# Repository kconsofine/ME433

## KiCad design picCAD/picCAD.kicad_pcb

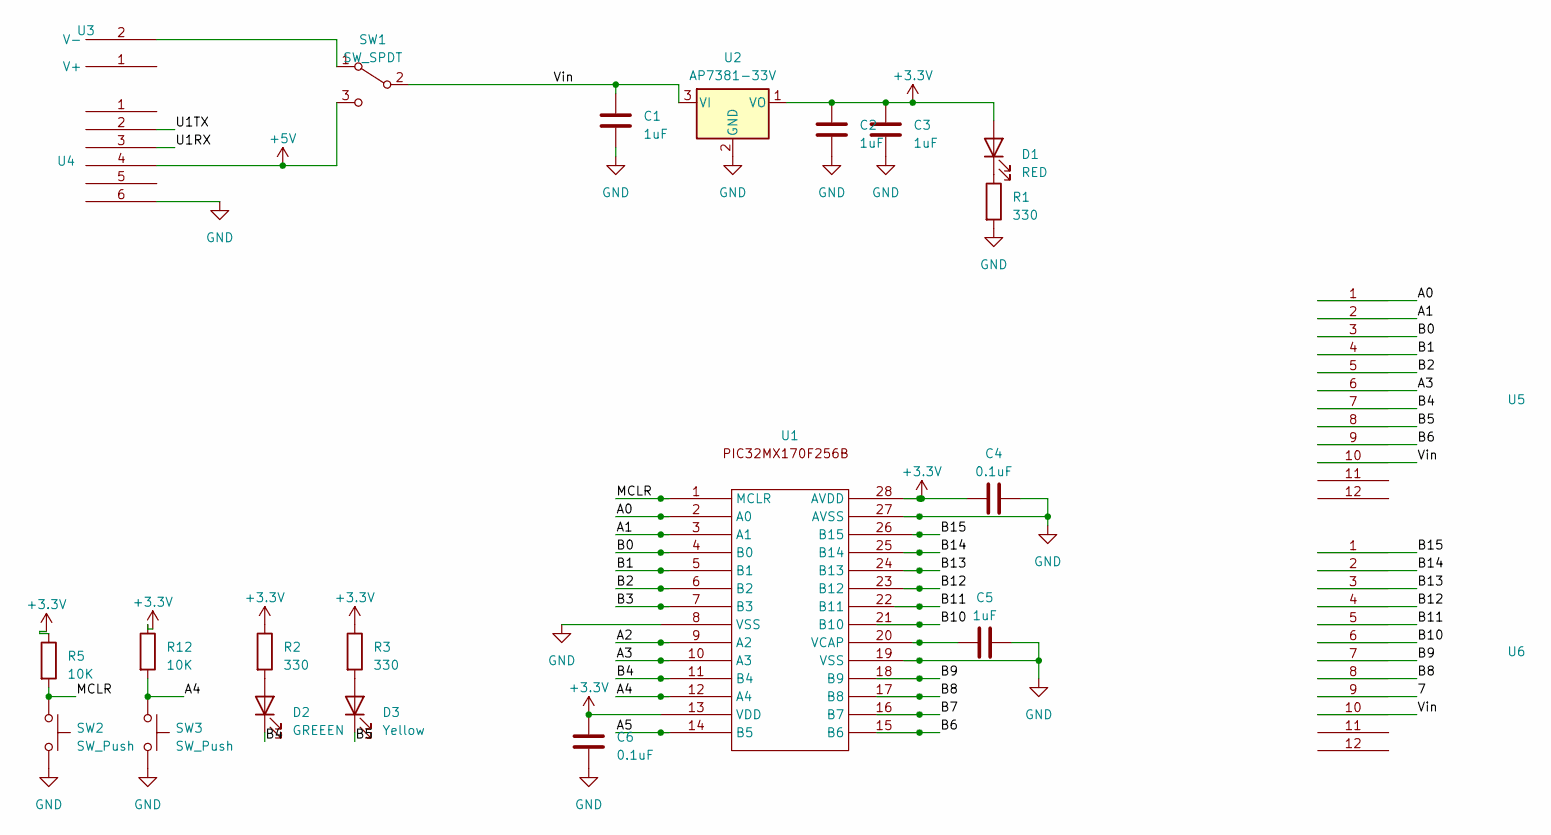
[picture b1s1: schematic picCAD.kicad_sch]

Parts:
C1, C2, C3, C5: 1uF; C_Disc_D3.8mm_W2.6mm_P2.50mm
C4, C6: 0.1uF; C_Disc_D3.8mm_W2.6mm_P2.50mm
D1: RED; LED_D3.0mm
D2: GREEEN; LED_D3.0mm
D3: Yellow; LED_D3.0mm
R1, R2, R3: 330; R_Axial_DIN0207_L6.3mm_D2.5mm_P7.62mm_Horizontal
R5, R12: 10K; R_Axial_DIN0207_L6.3mm_D2.5mm_P7.62mm_Horizontal
SW1: SW_SPDT; slide2
SW2, SW3: SW_Push; push button
U1: DIP-28_W7.62mm_Socket
U2: AP7381-33V; TO-92L_Inline
U3: PinSocket_1x02_P2.54mm_Vertical
U4: PinSocket_1x06_P2.54mm_Vertical
U5, U6: PinSocket_1x12_P2.54mm_Vertical

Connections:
+3.3V: C2.1, C3.1, C4.1, C6.2, D1.2 (A), R2.1, R3.1, R5.1, R12.1, U1.13 (VDD), U1.28 (AVDD), U2.1 (VO)
+5V: SW1.3 (C), U4.4
/7: U6.9
/A0: U1.2 (A0), U5.1
/A1: U1.3 (A1), U5.2
/A2: U1.9 (A2)
/A3: U1.10 (A3), U5.6
/A4: R12.2, SW3.1, U1.12 (A4)
/A5: U1.14 (B5)
/B0: U1.4 (B0), U5.3
/B1: U1.5 (B1), U5.4
/B2: U1.6 (B2), U5.5
/B3: U1.7 (B3)
/B4: D2.1 (K), U1.11 (B4), U5.7
/B5: D3.1 (K), U5.8
/B6: U1.15 (B6), U5.9
/B7: U1.16 (B7)
/B8: U1.17 (B8), U6.8
/B9: U1.18 (B9), U6.7
/B10: U1.21 (B10), U6.6
/B11: U1.22 (B11), U6.5
/B12: U1.23 (B12), U6.4
/B13: U1.24 (B13), U6.3
/B14: U1.25 (B14), U6.2
/B15: U1.26 (B15), U6.1
/MCLR: R5.2, SW2.1, U1.1 (MCLR)
/U1RX: U4.3
/U1TX: U4.2
/Vin: C1.1, SW1.2 (B), U2.3 (VI), U5.10, U6.10
GND: C1.2, C2.2, C3.2, C4.2, C5.2, C6.1, R1.2, SW2.2, SW3.2, U1.8 (VSS), U1.19 (VSS), U1.27 (AVSS), U2.2 (GND), U4.6
unnamed: D1.1 (K), R1.1
unnamed: D2.2 (A), R2.2
unnamed: D3.2 (A), R3.2
unnamed: SW1.1 (A), U3.2 (V-)
unnamed: C5.1, U1.20 (VCAP)

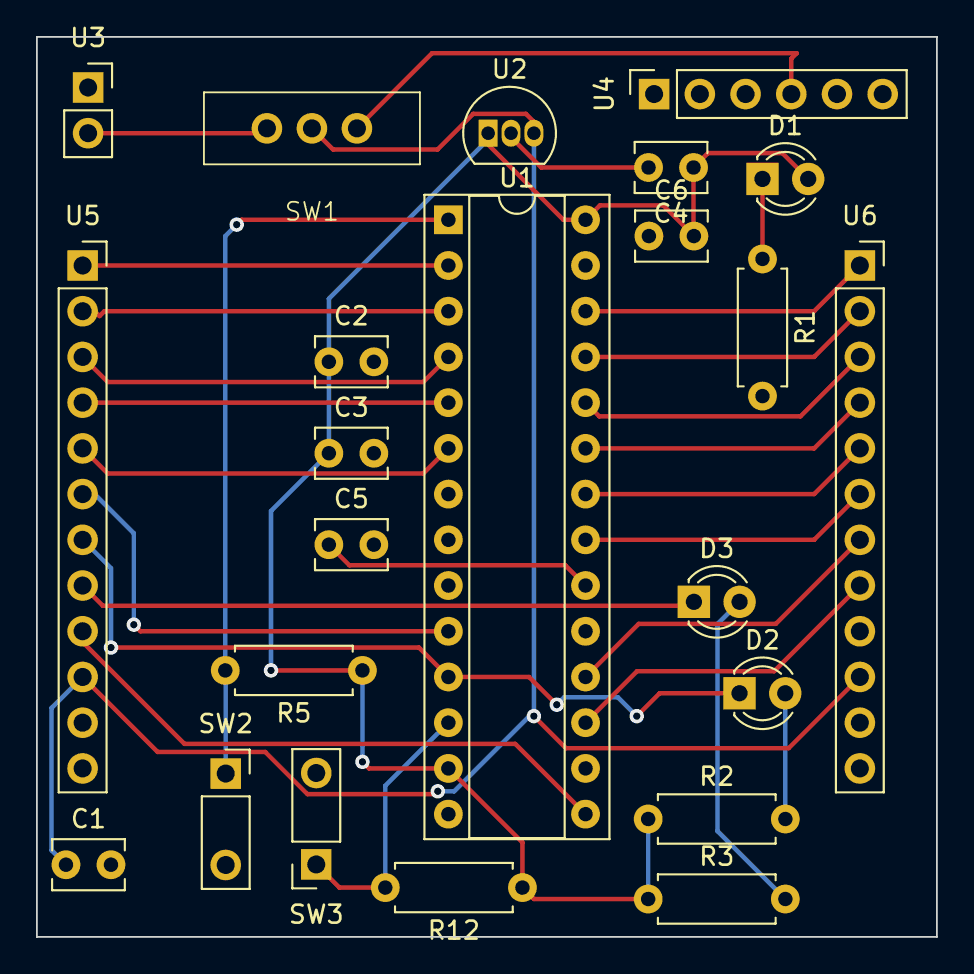
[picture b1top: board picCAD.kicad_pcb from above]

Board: 2 copper layers, 50.0 x 50.0 mm, 23 parts (0 on the bottom side), 28 nets.

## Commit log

2023-04-19 lkjdsf
2023-04-19 vid and pictures
2023-04-19 4/18/2023
2023-05-09 5/9/23
2023-06-01 june 1
2023-06-08 june 7
